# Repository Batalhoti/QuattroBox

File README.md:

# QuattroBox

<p align="center">
<p align="center">
<p align="center">

## Description

QuattroBox v2 is the complete evolution of my MMU for 3D printers.
This version has been fully redesigned from the ground up, focusing on simplicity, compactness, and everyday usability.

I kept as much compatibility as possible with components from the previous version, while introducing significant improvements in both mechanical design and overall user experience.

## Key features
- Integrated filament dryer with AC heater
- Exhaust system for moisture removal
- Dedicated 4A power supply (optional)
- More compact extruder using a 23 mm NEMA17 (pancake)
- Hub with integrated Sync PSF
- Hinged lid (compatible with v1 panels)
- Magnetic bottom cover for easy access and maintenance
- Simplified and more organized assembly process
- All electronic components are assembled outside the enclosure before final installation
- Cable management clips
- Fully 3D printed structure (no aluminum extrusions required)
- Mounting supports to rest the MMU on the printer’s top extrusions
- Optimized for a 180 mm print area, with up to 142 mm height
- Compatible with [**Happy Hare**](https://github.com/moggieuk/Happy-Hare/wiki) for MMU control 

### Design and usability

The QuattroBox v2 design has also evolved significantly, not only in aesthetics but mainly in everyday usability. The status LED buttons are part of the system’s visual and functional identity, making it easy to quickly understand its operation. The system also features dedicated lighting to monitor the filament path. The internal layout has been reorganized to be cleaner and more intuitive, improving both assembly and maintenance. Access to components has also been designed to be simpler and more practical for day-to-day use.

### Design philosophy

QuattroBox v2 was designed to be accessible and easy to build, without compromising functionality.
The goal is to eliminate unnecessary complexity while maintaining a reliable and efficient multi-material system.  

##

I have a Discord channel on [HappyHare](https://discord.gg/pGSMCnBXc7), feel free to ask your questions and give suggestions

E se voce é brasileiro tenho um canal no servidor da [Orion 3D](https://discord.gg/Ap2ZFJXG7s)

## 

[BOM V2](https://docs.google.com/spreadsheets/d/1JrKG5omNthBb1Ab2Xag8QSc8Q7b502xr/edit?usp=sharing&ouid=110858727598242563373&rtpof=true&sd=true)

If you want to buy the complete kit

[SeleadLab v2 (Affiliate Link)](https://s.click.aliexpress.com/e/_c2JtqLK5)

[Trianglelab v2 (Affiliate Link)](https://s.click.aliexpress.com/e/_c4NRFI21)

## My build v1

[VIDEO 1](https://photos.app.goo.gl/y86quBDpxgd3wVg19)

[VIDEO 2](https://photos.app.goo.gl/qtu92ND3gbf3hNFr5)

<p align="center">
<p align="center">

## My build v2

Soon

## Acknowledgements

Special thanks to SkiBike for the [Filamentalist](https://github.com/Enraged-Rabbit-Community/ERCF_v2/tree/master/Recommended_Options/Filamentalist_Rewinder) design and to ArmoredTurtle for the [BoxTurtle](https://github.com/ArmoredTurtle/BoxTurtle) design, both of which inspired this project.
I also thank Diem who helped me with the publication here on GitHub

### [Change log](ChangeLog.md)

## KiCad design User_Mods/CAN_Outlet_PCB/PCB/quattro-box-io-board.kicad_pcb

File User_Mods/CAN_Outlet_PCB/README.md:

# CAN PCB for simplified wiring

A custom PCB to simplify wiring of the CAN outlet.

The Chameleon X5 comes with an IO Board, but it is not used for the QuattroBox.

**Important**: The MicroFit 3.0 pinout of the PCB differs compared to the Chameleon X5 IO Board.
This is to match the pinout used by the EBB36 GEN2.

## BOM

- 1x XT30PW-M: [tme](https://www.tme.eu/de/details/xt30pw-m/dc-steckverbinder/amass/), [LCSC](https://www.lcsc.com/product-detail/C30170175.html)
- 2x MX-43045-0412: [tme](https://www.tme.eu/de/details/mx-43045-0412), [LCSC](https://www.lcsc.com/product-detail/C277721.html)
- 1x NUP2105L: [tme](https://www.tme.eu/de/details/nup2105l-dio), [LCSC](https://www.lcsc.com/product-detail/C14486.html)
- 1x SMBJ26A: [tme](https://www.tme.eu/de/details/p6smbj26a-dio), [LCSC](https://www.lcsc.com/product-detail/C726831.html)
- 1x Fuse in 1206 form factor: [tme](https://www.tme.eu/de/details/tr-3216ff4-r), [LCSC](https://www.lcsc.com/product-detail/C41367229.html)
- 1x JST XH 2 Pin connector: [tme](https://www.tme.eu/de/details/b2b-xh-a), [LCSC](https://www.lcsc.com/product-detail/C158012.html)

The board will function without the NUP2105L (protect CAN L/H against ESD) and SMBJ26A (protect against voltage ripples), the other parts are required.

For assembly:
- 3x M3x8mm screws
- 3x M3x4x5 heatset insert (the standard voron heatset inserts)

### Fuse

A fuse is supposed to cut an electrical connection when the current flowing through it exceeds a limit. After this happens, the fuse has to be replaced.
This is useful in case of for example a short-circuit where a large amount of current may flow, which can destroy components that are unable to handle
the current.

The Chameleon X5 IO Board uses a 20A fuse. The issue is that neither the MicroFit 3.0 nor the DC barrel jack are rated
to supply anywhere near 20A of power. Most MicroFit 3.0 connector are rated for 5A, there are some (like the one used in this board)
that are rated for 8.5A per pin. The DC barrel jack is rated for up to 3A.

If you want to have the fuse protect your hardware (e.g. it should blow before the connector melts), I would **not** install a 20A fuse.

As more current passes through a component, it will heat up. For the MicroFit 3.0 connector, the [Product Specification](https://www.molex.com/content/dam/molex/molex-dot-com/products/automated/en-us/productspecificationpdf/430/43045/PS-43045-001.pdf?inline)
shows on page 9 how much current could pass through the connector before it heats up by more than 30°C.
This depends on the cable diameter, how many wires are used, and the ambient temperature.

For the common use-case where the heaters are powered through AC, it is unlikely that the Chameleon X5 will pull
anywhere close to the 8.5A. I would recommend a fuse in the range of 4A to 8A.

Another use-case may be to install e.g. 70W @ 24V DC heaters, which are then powered and controlled through the Chameleon X5.
With each heater pulling ~2.9A, and the Chameleon X5 using some power too, I would suggest an 8A to 10A fuse. 

## Print settings

No special print settings are necessary. The parts are **not** shrinkage compensated.
For the spacer I would recommend a brim.

## PCB

The PCB has been designed in KiCAD10, the project files are located in [PCB](PCB).

The gerber files for ordering a PCB, can be found in [PCB/production/quattro-box-io-board.zip](PCB/production/quattro-box-io-board.zip).
It is a 2 layer board. I have ordered the parts myself, and assembled it by hand, therefore the `bom.csv` is incomplete or may contain
unavailable parts. No special consideration has been made to use jlc basic parts (the parts without extra costs),
therefore I recommend assembling it yourself.

## Assembly

Three heatset inserts must be installed into this part. After you have done that, screw in the USB C connector (like in the original part with the M2 screws),
then seat it from the outside of the box:

To avoid wobbling, there is a spacer that should now be installed:

Then install the PCB:

Add the PCB cover and add the 3 screws to hold everything together:

## More images

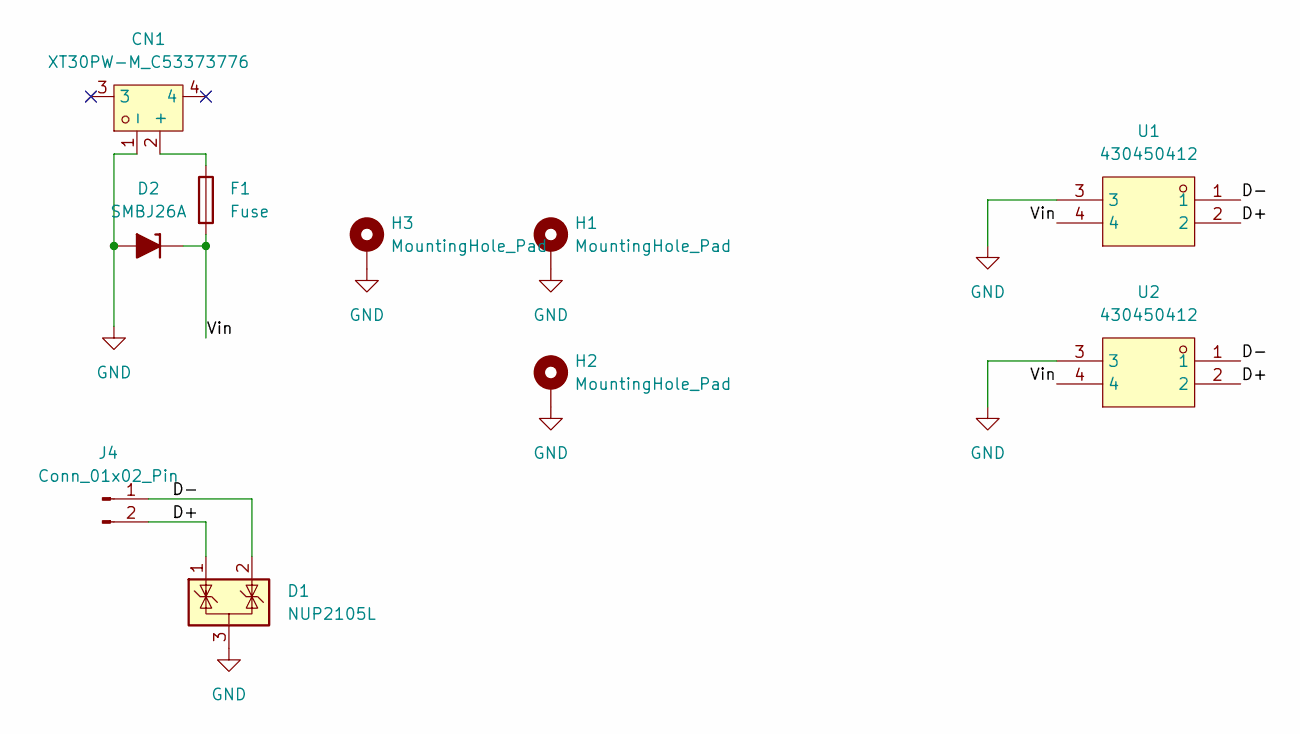
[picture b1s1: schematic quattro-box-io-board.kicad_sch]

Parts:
CN1: XT30PW-M_C53373776; CONN-TH_XT30PW-M; MPN XT30PW-M; LCSC Part C53373776
D1: NUP2105L; SOT-23
D2: SMBJ26A; D_SMB
F1: Fuse; Fuse_1206_3216Metric_Pad1.42x1.75mm_HandSolder
H1, H2, H3: MountingHole_Pad; MountingHole_3.2mm_M3_DIN965_Pad_TopBottom
J4: Conn_01x02_Pin; JST_XH_B2B-XH-A_1x02_P2.50mm_Vertical
U1, U2: 430450412; CONN-TH_4P-P3.00-S3.00_L7.4-W9.7-EH9.0; MPN 430450412; LCSC Part C277721

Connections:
/D+: D1.1 (K), J4.2, U1.2, U2.2
/D-: D1.2 (K), J4.1, U1.1, U2.1
/Vin: D2.1 (K), F1.2, U1.4, U2.4
GND: CN1.1 (-), D1.3 (A), D2.2 (A), H1.1 (1_1), H2.1 (1_1), H3.1 (1_1), U1.3, U2.3
unnamed: CN1.2 (+), F1.1

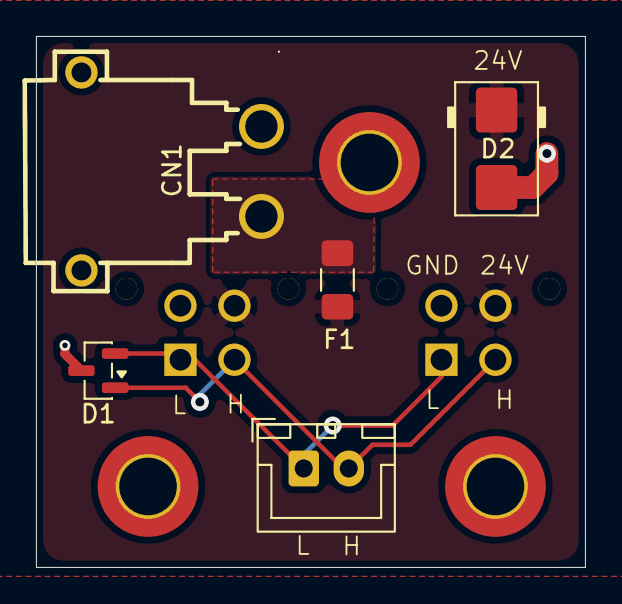
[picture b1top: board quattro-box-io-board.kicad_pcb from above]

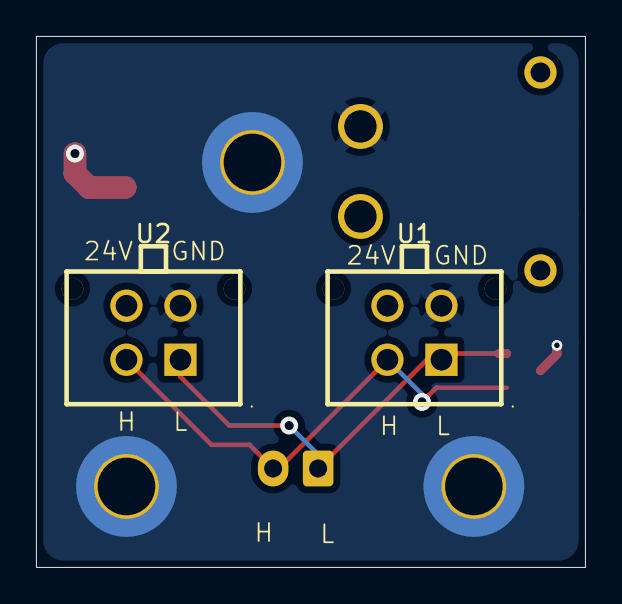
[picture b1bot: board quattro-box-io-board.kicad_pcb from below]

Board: 2 copper layers, 30.5 x 29.5 mm, 10 parts (2 on the bottom side), 5 nets.

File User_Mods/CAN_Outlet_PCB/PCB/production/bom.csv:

Designator,Footprint,Quantity,Value,LCSC Part #
CN1,CONN-TH_XT30PW-M,1,XT30PW-M_C53373776,C53373776
D1,SOT-23,1,NUP2105L,
D2,D_SMB,1,SMBJ26A,
F1,1206,1,Fuse,
J4,JST_XH_B2B-XH-A_1x02_P2.50mm_Vertical,1,Conn_01x02_Pin,
"U1, U2",CONN-TH_4P-P3.00-S3.00_L7.4-W9.7-EH9.0,2,430450412,C277721

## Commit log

2025-01-11 First public release
2025-01-11 fixes
2025-01-11 add my build
2025-01-11 add macro rewinder
2025-01-11 fixes names
2025-01-11 fixes links
2025-01-11 updade readme.md
2025-01-13 extruder update
2025-01-16 Update box and tensioner
2025-01-18 pinout modification
2025-01-31 Update new stls
2025-01-31 Update new CAD
2025-03-09 Latch and Extruder Corrections
2025-03-30 Updade readme
2025-03-30 Updade config
2025-04-02 fix encoder
2025-04-21 enclosure
2025-05-17 update tools
2025-05-20 update wire size
2025-05-21 fix readme.md
2025-05-22 fix pinout
2025-05-28 Top mounting printer
2025-06-18 removed led soldering jig
2025-06-18 removed led welding template and updated ptfe tools
2025-06-23 Manual Assembly v1.0
2026-02-16 Beta_v2
2026-02-16 update cad v2
2026-04-06 Add missing DXF files for Quattrobox V2 side panels (closes #9)
2026-04-15 Release V2
2026-04-15 fix changelog hyperlink
2026-04-16 Tensioner corrections
2026-04-16 update change log
2026-04-16 Update CAD
2026-04-16 Filename correction
2026-05-04 image update
